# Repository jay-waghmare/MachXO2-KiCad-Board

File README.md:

# MachXO2-640HC FPGA Breakout Board - KiCad Design 🛠️

> Custom breakout board for Lattice **LCMXO2-640HC-6MG132I** - Designed in KiCad 9.0.3 - 8 Sheets Hierarchical - By Jay Waghmare

<p align="center">
  
  <br><em>3D Render - MachXO2-640HC Board (KiCad 3D View)</em>
</p>

## 🌟 What Is This? (From My Schematic PDF)

Custom FPGA development board designed from scratch in KiCad for **Lattice MachXO2 LCMXO2-640HC-6MG132I** (640 LUTs, 132-ball CSBGA).

**Full breakout board, not simple LED:**

- USB Mini-B (J1) for power + data with ESD protection USBLC6-2SC6 (U2)
- Dual LDO: 5V→3.3V TL1963A-33DCYR (U4) and 5V→1.2V LD1117S12CTR (U5) for core + I/O
- FT231XQ USB-UART bridge (U7) for serial
- JTAG header 1x10 (J2) for Lattice HW-USBN-2B programmer (10 flywires - White TCK, Orange TDI, Brown TDO, Purple TMS...)
- All 4 I/O Banks broken out: Bank0 Top (PT6A...), Bank1 Right (PR28... LVDS), Bank2/3 Left (PL2A...), Bank Bottom (PB4A...) + GND/NC
- Power LEDs D1 D2, User LEDs, Button SW1 for PROGRAMN

Why I made my own? To learn FPGA hardware - Power sequencing, decoupling, JTAG, I/O banks.

**8 Sheets Hierarchical (KiCad 9.0.3, file MACHXO2_test.kicad_sch):**

| Sheet | File | Content |
|-------|------|---------|
| 1/8 | MACHXO2_test.kicad_sch | Top Level - Power, User_IO/Banks, Device_Management blocks |
| 2/8 | Power.kicad_sch | Power: USB Mini, 3.3V/1.2V LDOs, FPGA VCC/VCCIO decoupling C6 0.1uF C7 4.7uF etc, VCCIO table |
| 3/8 | USER_IO_Bank_T | Bank0 Top - U6B LCMXO2 Bank0, JTAG TDO/TDI/TCK/TMS, J3 12-pin socket |
| 4/8 | USER_IO_Bank_R | Bank1 Right - U6C Bank1, LVDS1/2/3, PCLK, J4 10-pin header |
| 5/8 | USER_IO_Bank_L | Bank Left - U6D Bank Left PL2A...PL7B |
| 6/8 | USER_IO_Bank_B | Bank Bottom - U6E Bank Bottom PB4A...PB14B |
| 7/8 | USER_Config | Config - JTAG J2, PROGRAMN button SW1, FT231XQ UART, JTAG header flywire table |
| 8/8 | GND&NC | GND & NC - U6F/U6G NC pins and GND balls |

## ✨ Board Features (From Schematic)

- **FPGA:** U6 LCMXO2-640HC-6MG132I, 640 LUTs, MG132I, Speed 6
- **Power:** J1 USB Mini-B, D3 1N5819HW?, U2 USBLC6-2SC6 ESD, U4 TL1963A-33DCYR 5V→3.3V (C2 4.7uF, C3 10uF, C21 10uF), U5 LD1117S12CTR 5V→1.2V (C22 4.7uF, C23 10uF, C24 10uF), D1 D2 power LEDs with R8 1K, C6 0.1uF C7 4.7uF per +1V2, C8 0.1uF C10 1uF C9 4.7uF per +3V3 bank - Proper decoupling!
- **Recommended VCCIO (Your Table):** PB left 3.3V (sensors, SPI flash), PL lower 1.8V (low-voltage memory), PR right 1.8V/2.5V (high-speed), PT top 3.3V (UART, SPI, USB-UART)
- **JTAG:** J2 1x10 header, R6 R7 R8 22R series for TDO/TDI/TCK/TMS, R11 4K7 pull-up for PROGRAMN, SW1 dual push button, Notes: INITN B13 open-drain float OK, JTAGENB B9 float OK (internal weak pull-up)
- **UART:** U7 FT231XQ with C26 4.7uF C27 0.1uF C28 0.1uF, TXD_FTDI, RXD_FTDI, RTS_FTDI, CTS, VBUS detection R1 4K7 + R13 10K divider
- **JTAG Programmer:** Lattice HW-USBN-2B USB cable with 10 flywire - Official tool - TCK White 4.7K to GND, TDI Orange 22R series, TDO Brown direct, TMS Purple 22R series, GND Black, VCC Red 0.1uF, PROGRAMN Yellow 4.7K+btn, DONE Blue LED+330Ω, INITN Green float, JTAGENB Gray float

## 📁 Files (Your Actual Uploads - Live)

**You uploaded:** .kicad_pro, .kicad_sch, .kicad_pcb, .kicad_prl, schematic.pdf, 3d-render.png, pcb_preview.png - Full project!

## 📸 Photos / Renders

| Schematic PDF | PCB Preview | 3D Render |
|---------------|-------------|-----------|
| [schematic.pdf](hardware/schematics/schematic.pdf) (8 pages) |  |  |

## 📦 How to View

1. Install KiCad 9.0.3: https://kicad.org/download/
2. Clone: git clone https://github.com/jay-waghmare/MachXO2-KiCad-Board.git
cd MachXO2-KiCad-Board
3. Open `MACHXO2_test.kicad_pro` → Schematic Editor (8 sheets) → PCB Editor → 3D View

## 🗺️ Roadmap

- [x] KiCad hierarchical schematic 8 sheets - LCMXO2-640HC - Done (your PDF)
- [x] Upload .kicad_pro, .kicad_sch, .kicad_pcb, .kicad_prl - Done (5-6 greens today!)
- [x] Upload schematic.pdf + 3D renders - Done 5 mins ago!
- [ ] Add hardware/bom.md with exact values from schematic
- [ ] Add docs/design.md - Why 640HC, why TL1963A + LD1117, why 132-ball
- [ ] Export Gerbers: File → Fabrication Outputs → Gerbers → hardware/pcb/gerbers.zip
- [ ] Fabricate at JLCPCB
- [ ] Bring-up: Power test 3.3V/1.2V, JTAG scan with HW-USBN-2B, first blinky
- [ ] Add real board photos

## 👨‍💻 Author

**Jay Waghmare** - FPGA 
- GitHub: [@jay-waghmare](https://github.com/jay-waghmare) 
- Board: LCMXO2-640HC-6MG132I custom breakout - Designed from scratch in KiCad 9.0.3

If you like FPGA hardware boards, please ⭐ star!

## 📄 License

MIT License

> Designed from scratch in KiCad 9.0.3

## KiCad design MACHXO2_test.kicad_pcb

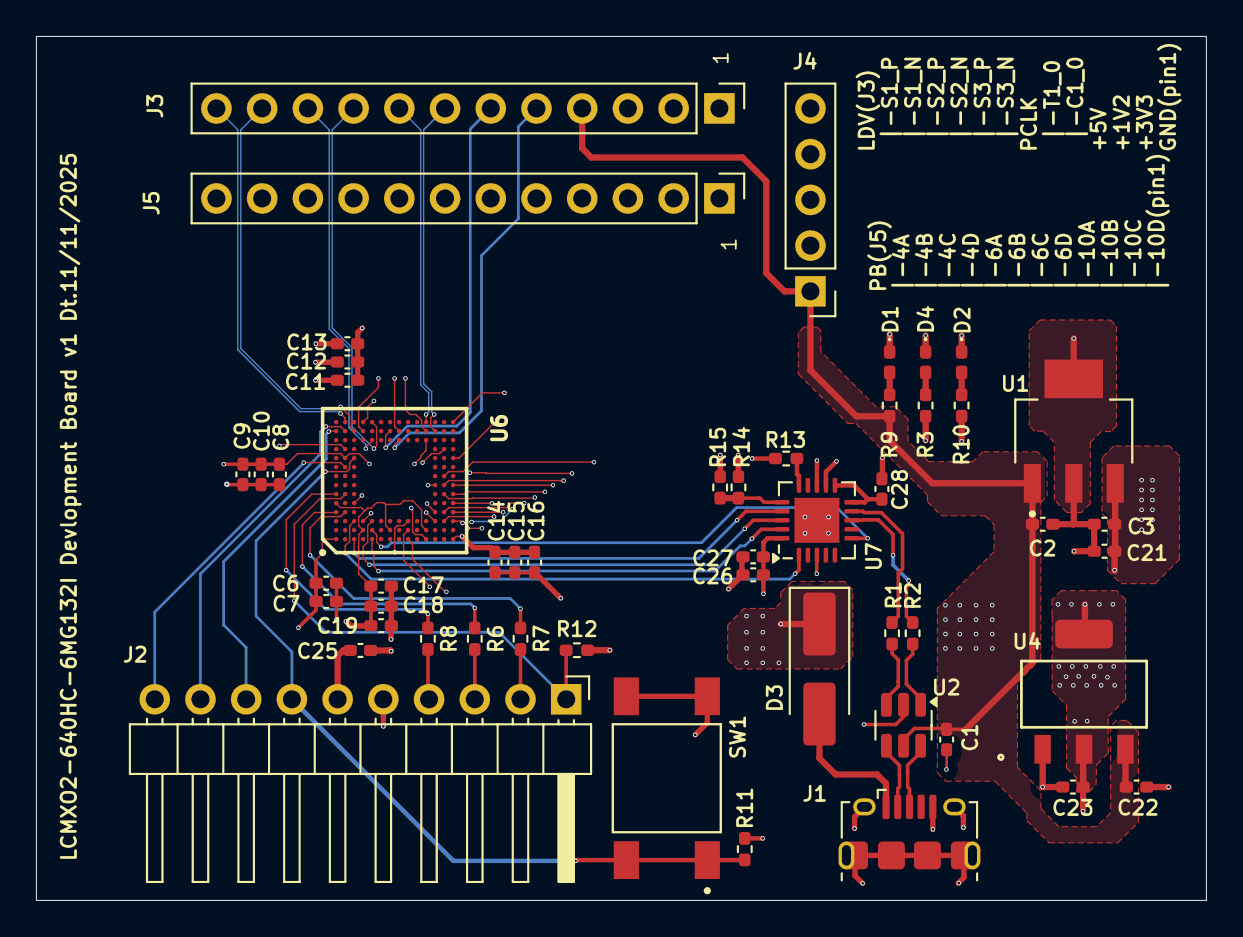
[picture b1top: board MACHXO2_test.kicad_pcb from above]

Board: 4 copper layers, 65.0 x 48.0 mm, 52 parts (0 on the bottom side), 56 nets.

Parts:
C1, C6, C8, C11, C14, C17, C25, C27, C28: 0.1uf; C_0402_1005Metric_Pad0.74x0.62mm_HandSolder
C2, C7, C9, C13, C16, C19, C22, C26: 4.7uf; C_0402_1005Metric_Pad0.74x0.62mm_HandSolder
C3, C21, C23: 10uf; C_0402_1005Metric_Pad0.74x0.62mm_HandSolder
C10, C12, C15, C18: 1uf; C_0402_1005Metric_Pad0.74x0.62mm_HandSolder
D1, D2, D4: LED; LED_0402_1005Metric_Pad0.77x0.64mm_HandSolder
D3: 1N5819HW; D_SMA_Handsoldering
J1: USB_B_Mini; USB_Micro-B_Amphenol_10118194-0001LF_Horizontal
J2: Conn_01x10_Pin; PinHeader_1x10_P2.54mm_Horizontal
J3, J5: Conn_01x12_Pin; PinHeader_1x12_P2.54mm_Vertical
J4: Conn_01x05_Pin; PinHeader_1x05_P2.54mm_Vertical
R1, R2, R6, R7, R8: 22R; R_0402_1005Metric_Pad0.72x0.64mm_HandSolder
R3, R9, R10: 1K; R_0402_1005Metric_Pad0.72x0.64mm_HandSolder
R11, R12, R14: 4K7; R_0402_1005Metric_Pad0.72x0.64mm_HandSolder
R13, R15: 10K; R_0402_1005Metric_Pad0.72x0.64mm_HandSolder
SW1: SW_Push_Dual; SW_TL3301AF160QG
U1: TL1963A-33DCYR; VREG_TL1963A-33DCYR
U2: USBLC6-2SC6; SOT-23-6
U4: LD1117S12CTR; SOT-223_STM
U6: LCMXO2-640HC-6MG132I; BGA132C50P14X14_800X800X135
U7: FT231XQ; QFN-20-1EP_4x4mm_P0.5mm_EP2.5x2.5mm

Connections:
+1V2: C6.1, C7.1, C23.1, J3.3, R3.2, U4.2 (VOUT), U6.A1 (VCC_1), U6.P14 (VCC_2)
+3V3: C3.1, C8.1, C9.1, C10.1, C11.1, C12.1, C13.1, C14.1, C15.1, C16.1, C17.1, C18.1, C19.1, C21.1, C25.2, C26.1, C27.1, J2.6, J3.2, R10.2, R11.2, U1.3 (OUT), U6.B10 (VCCIO0_1), U6.C5 (VCCIO0_2), U6.D3 (VCCIO3_1), U6.D14 (VCCIO1_1), U6.L1 (VCCIO3_2), U6.L12 (VCCIO1_2), U6.N11 (VCCIO2_1), U6.P1 (VCCIO2_2), U7.12 (VCC), U7.20 (VCCIO)
/Power/D+: R2.1, U2.1 (I/O1)
/Power/D-: R1.1, U2.3 (I/O2)
/Power/USBD_N: J1.2 (D-), U2.4 (I/O2)
/Power/USBD_P: J1.3 (D+), U2.6 (I/O1)
/USER_IO_Bank_R/LDVS1_N: J3.11, U6.C13 (PR2B)
/USER_IO_Bank_R/LDVS1_P: J3.12, U6.B14 (PR2A)
/USER_IO_Bank_R/LDVS2_N: J3.9, U6.E14 (PR2D)
/USER_IO_Bank_R/LDVS2_P: J3.10, U6.E12 (PR2C)
/USER_IO_Bank_R/LDVS3_N: J3.7, U6.M13 (PR7B)
/USER_IO_Bank_R/LDVS3_P: J3.8, U6.L14 (PR7A)
/USER_IO_Bank_R/PCLKC1_0: J3.5, U6.H12 (PR5D)
/USER_IO_Bank_R/PCLKT1_0: J3.6, U6.G13 (PR5C)
A4: R6.1, U6.A4 (PT7A)
A6: R8.1, U6.A6 (PT7D)
B4: R7.1, U6.B4 (PT7B)
CLK: J4.4, U6.J3 (PL6C)
CS: J4.3, U6.J2 (PL6B)
CTS_FTDI: U6.E2 (PL3B), U7.6 (~CTS)
DIN: J4.2, U6.J1 (PL6A)
DONE: J2.8, U6.A13 (PT11D)
DTR_FTDI: U6.E3 (PL3C), U7.18 (~DTR)
D_N: R1.2, U7.9 (USBDM)
D_P: R2.2, U7.8 (USBDP)
GND: C1.2, C2.2, C3.2, C6.2, C7.2, C8.2, C9.2, C10.2, C11.2, C12.2, C13.2, C14.2, C15.2, C16.2, C17.2, C18.2, C19.2, C21.2, C22.2, C23.2, C25.1, C26.2, C27.2, C28.2, D1.1 (K), D2.1 (K), D4.1 (K), J1.5 (GND), J1.6 (Shield), J2.5, J3.1, J4.5, R12.2, R13.2, R15.1, SW1.2, SW1.4, U1.2 (GND), U2.2 (GND), U4.1 (GND), U6.A5 (GND_1), U6.B11 (GND_2), U6.D2 (GND_3), U6.D13 (GND_4), U6.G2 (GND_5), U6.H13 (GND_6), U6.L2 (GND_7), U6.L13 (GND_8), U6.P5 (GND_9), U6.P10 (GND_10), U7.3 (GND), U7.13 (GND), U7.21 (GND)
INITN: J2.9, U6.B13 (PT11C)
JTAGENB: J2.10, U6.B9 (PT10C)
M3: J5.11, U6.M3 (PB4B)
M4: J5.8, U6.M4 (PB6A)
M7: J5.2, U6.M7 (PB10C)
N3: J5.10, U6.N3 (PB4C)
N4: J5.7, U6.N4 (PB6B)
N6: J5.6, U6.N6 (PB6C)
N7: J5.3, U6.N7 (PB10B)
N8: J5.1, U6.N8 (PB10D)
unnamed: D1.2 (A), R9.1
unnamed: D2.2 (A), R10.1
unnamed: D3.2 (A), J1.1 (VBUS)
unnamed: D4.2 (A), R3.1
unnamed: C28.1, U7.10 (3V3OUT), U7.11 (~RESET)
unnamed: R13.1, U7.15 (CBUS0)
unnamed: R14.1, R15.2, U7.16 (CBUS3)
P3: J5.12, U6.P3 (PB4A)
P4: J5.9, U6.P4 (PB4D)
P6: J5.5, U6.P6 (PB6D)
P7: J5.4, U6.P7 (PB10A)
PROGRAMN: J2.7, R11.1, SW1.1, SW1.3, U6.C10 (PT10D)
RTS_FTDI: U6.E1 (PL3A), U7.19 (~RTS)
RXD_FTDI: U6.C3 (PL2B), U7.1 (RXD)
TCK: J2.1, R12.1, U6.B6 (PT7C)
TDI: J2.2, R7.2
TDO: J2.3, R6.2
TMS: J2.4, R8.2
TXD_FTDI: U6.C1 (PL2A), U7.17 (TXD)
VBUS: C1.1, C2.1, C22.1, D3.1 (K), J3.4, J4.1, R9.2, R14.2, U1.1 (IN), U2.5 (VBUS), U4.3 (VIN)
